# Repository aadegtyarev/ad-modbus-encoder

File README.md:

# ad-modbus-encoder
Modbus энкодер на ESP8266

## Прошивка
Прошивка написана в Arduino, исходники в `fw/src`, а бинарник в `fw/bin`. 

Для сборки из исходников, установите в Arduino библиотеки *modbus-esp8266* и
 *SimpleTimer*.

## Плата
### Схема для сборки
Схемы в формате PDF в `pcb/pdf-schematic/`.

### JLCPCB
Файлы для заказа плат на jlcpcb в `pcb/jlcpcb files`.

### Исходники
Исходники плат в `/pcb/src/`, для редактирования нужно:
1. [KiCad](https://www.kicad.org/) — среда проектирования.
2. Mini-360_DCDC_LM2596_module.kicad_mod — футпринт для Mini-360, лежит в `pcb/src/modules`.
3. [kicad-jlcpcb-tools](https://github.com/Bouni/kicad-jlcpcb-tools) — генерирует файлы для jlcpcb.

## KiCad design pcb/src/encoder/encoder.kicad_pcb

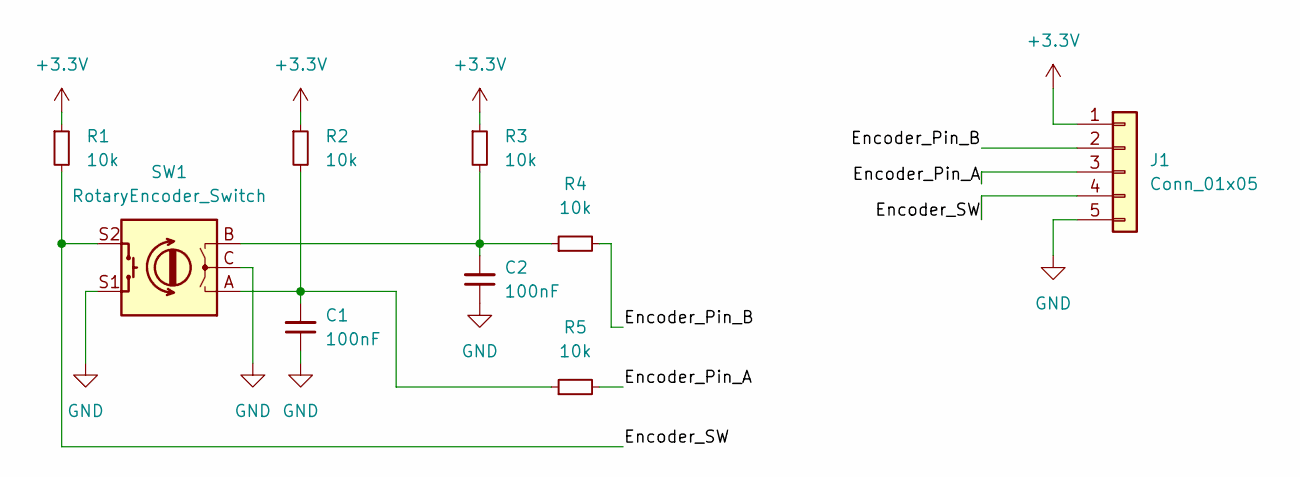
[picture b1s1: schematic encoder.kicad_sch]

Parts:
C1, C2: 100nF; C_0805_2012Metric
J1: Conn_01x05; SolderWire-0.1sqmm_1x05_P3.6mm_D0.4mm_OD1mm
R1, R2, R3, R4, R5: 10k; R_0805_2012Metric
SW1: RotaryEncoder_Switch; RotaryEncoder_Alps_EC11E-Switch_Vertical_H20mm_CircularMoun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

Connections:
+3.3V: J1.1, R1.1, R2.1, R3.1
/Encoder_Pin_A: J1.3, R5.2
/Encoder_Pin_B: J1.2, R4.2
/Encoder_SW: J1.4, R1.2, SW1.S2
GND: C1.1, C2.1, J1.5, SW1.C, SW1.S1
unnamed: C1.2, R2.2, R5.1, SW1.A
unnamed: C2.2, R3.2, R4.1, SW1.B

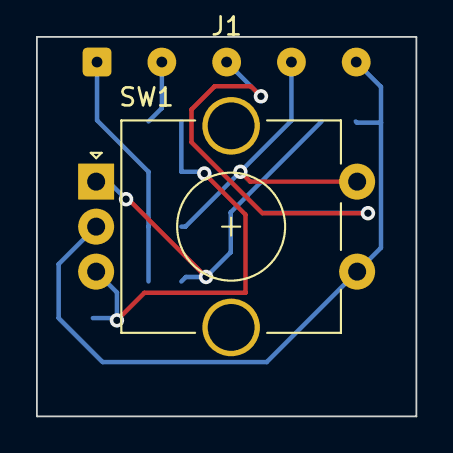
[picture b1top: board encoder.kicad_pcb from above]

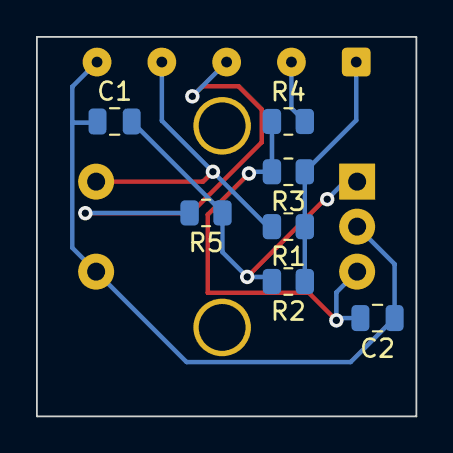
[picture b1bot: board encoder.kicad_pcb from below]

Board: 2 copper layers, 21.1 x 21.1 mm, 9 parts (7 on the bottom side), 7 nets.

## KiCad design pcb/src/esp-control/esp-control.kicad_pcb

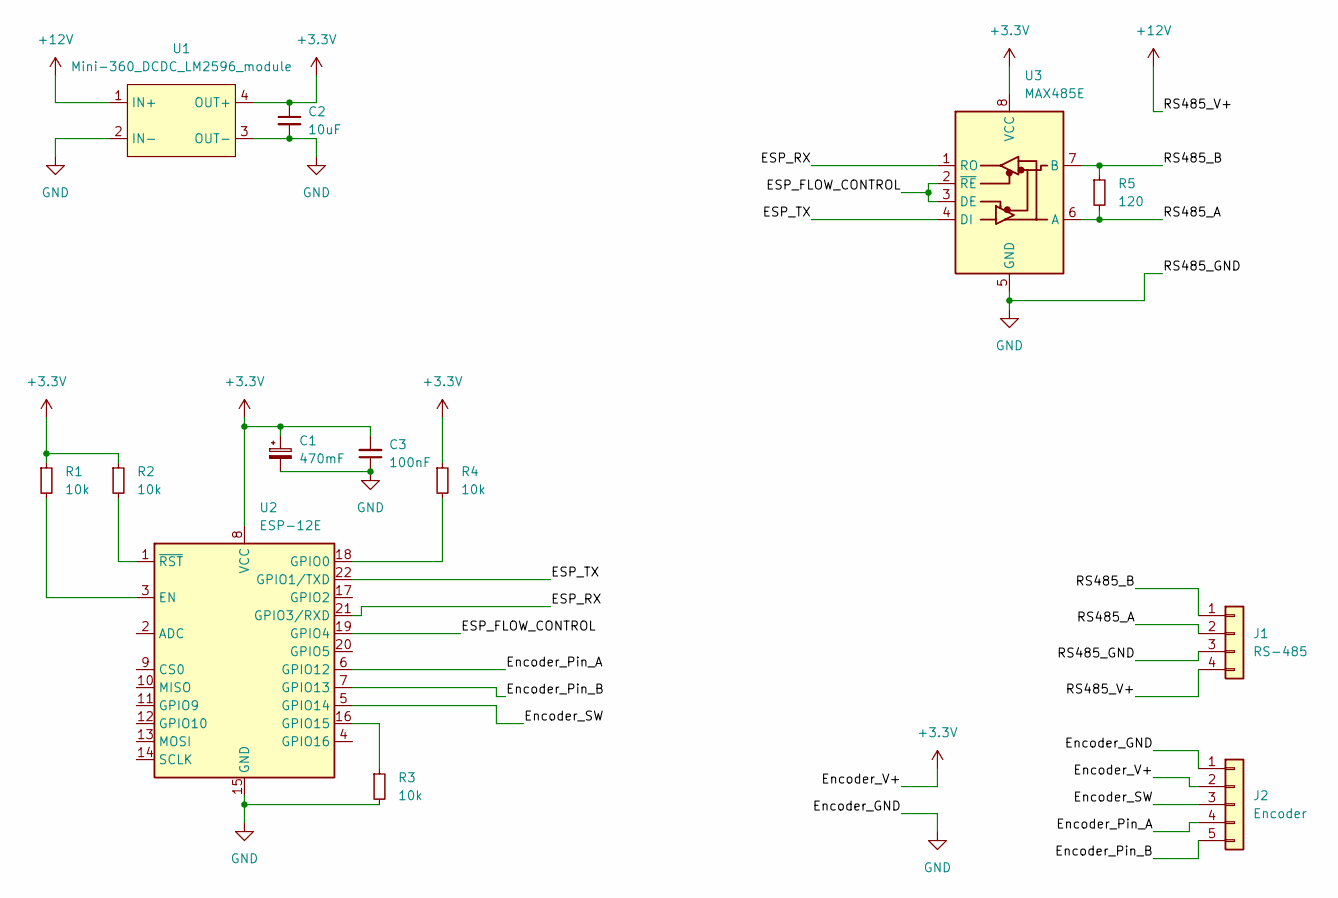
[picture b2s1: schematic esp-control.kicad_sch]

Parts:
C1: 470mF; CP_Radial_D6.3mm_P2.50mm
C2: 10uF; C_0805_2012Metric
C3: 100nF; C_0805_2012Metric
J1: RS-485; TerminalBlock_bornier-4_P5.08mm
J2: Encoder; PinHeader_1x05_P2.54mm_Vertical
R1, R2, R3, R4: 10k; R_0805_2012Metric
R5: 120; R_0805_2012Metric
U1: Mini-360_DCDC_LM2596_module
U2: ESP-12E
U3: MAX485E; DIP-8_W8.89mm_SMDSocket_LongPads

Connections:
+3.3V: C1.1, C2.1, C3.2, J2.2, R1.1, R2.1, R4.1, U1.4 (OUT+), U2.8 (VCC), U3.8 (VCC)
+12V: J1.4, U1.1 (IN+)
/ESP_FLOW_CONTROL: U2.19 (GPIO4), U3.2 (~RE), U3.3 (DE)
/ESP_RX: U2.21 (GPIO3/RXD), U3.1 (RO)
/ESP_TX: U2.22 (GPIO1/TXD), U3.4 (DI)
/Encoder_Pin_A: J2.4, U2.6 (GPIO12)
/Encoder_Pin_B: J2.5, U2.7 (GPIO13)
/Encoder_SW: J2.3, U2.5 (GPIO14)
/RS485_A: J1.2, R5.2, U3.6 (A)
/RS485_B: J1.1, R5.1, U3.7 (B)
GND: C1.2, C2.2, C3.1, J1.3, J2.1, R3.2, U1.2 (IN-), U1.3 (OUT-), U2.15 (GND), U3.5 (GND)
unnamed: R1.2, U2.3 (EN)
unnamed: R2.2, U2.1 (~RST)
unnamed: R3.1, U2.16 (GPIO15)
unnamed: R4.2, U2.18 (GPIO0)

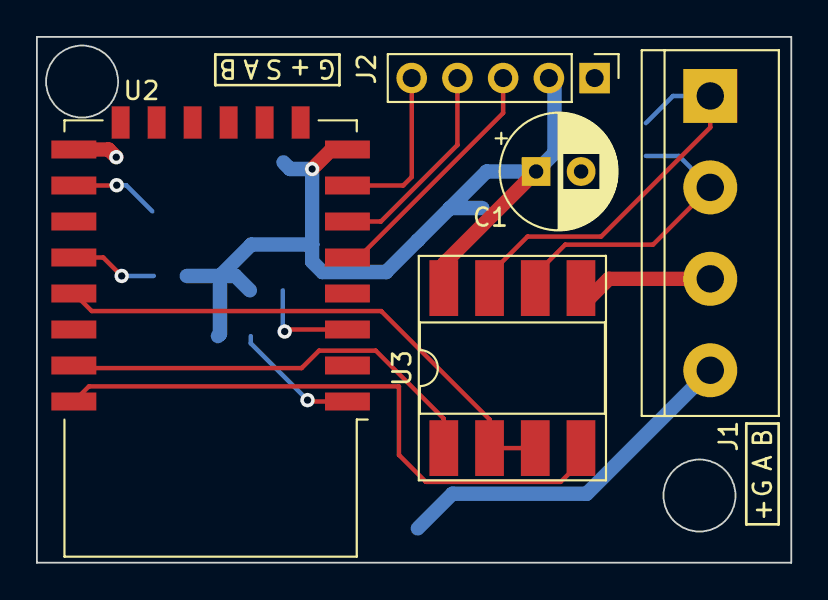
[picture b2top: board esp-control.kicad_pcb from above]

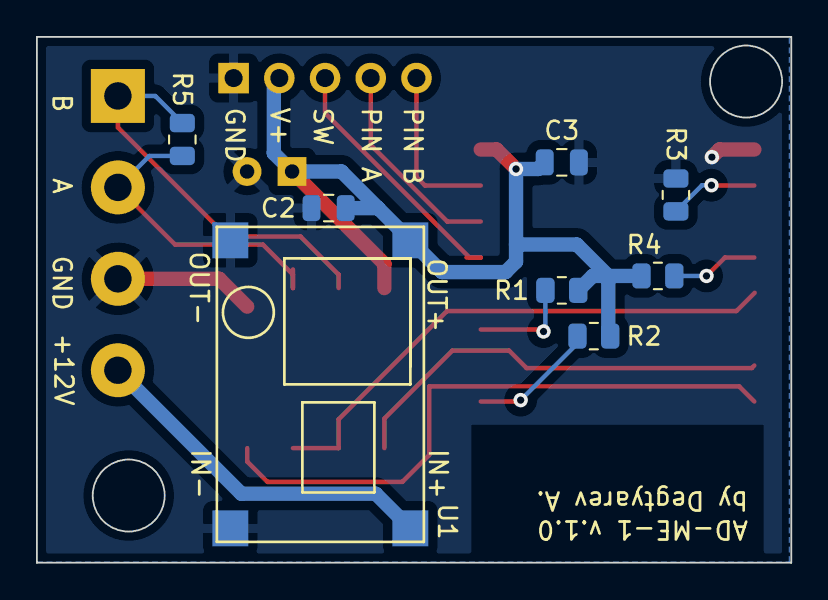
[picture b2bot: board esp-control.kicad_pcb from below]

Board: 2 copper layers, 41.9 x 29.2 mm, 13 parts (8 on the bottom side), 15 nets.

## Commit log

2022-12-10 init
2022-12-10 Вынес код в функции
2022-12-10 Добавил возможность менять адрес через регистр
2022-12-11 Добавил в схемы путь к репозиторию и версию. Добавил схемы в pdf.
2022-12-11 Добавил изменение скорости
2022-12-11 Убрал отладочный регистр
2022-12-11 Добавил сброс настроек подключения при нажатии на кнопку энкодера при старте.
2022-12-11 Доабвил бинарник и немного изменил структуру папки fw.
2022-12-17 Переписал почти всё. Теперь энкодер опрашивается по прерываниям.
2022-12-18 Поправил + обновил бинарник.
